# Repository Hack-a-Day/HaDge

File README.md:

# HaDge
=======
A wearable thing for Hackaday folks.

We're building a conference badge. No, we're not planning on organizing a Hackaday conference. It's for all the other conferences Hackaday goes to. If you have this badge, you're a member of an elite club, able to socialize in meatspace just as easily as you do on .io.

https://hackaday.io/project/3009-the-hackaday-badge

License
-------
[CERN Open Hardware Licence v1.2 ]

[CERN Open Hardware Licence v1.2 ]:http://www.ohwr.org/attachments/2388/cern_ohl_v_1_2.txt

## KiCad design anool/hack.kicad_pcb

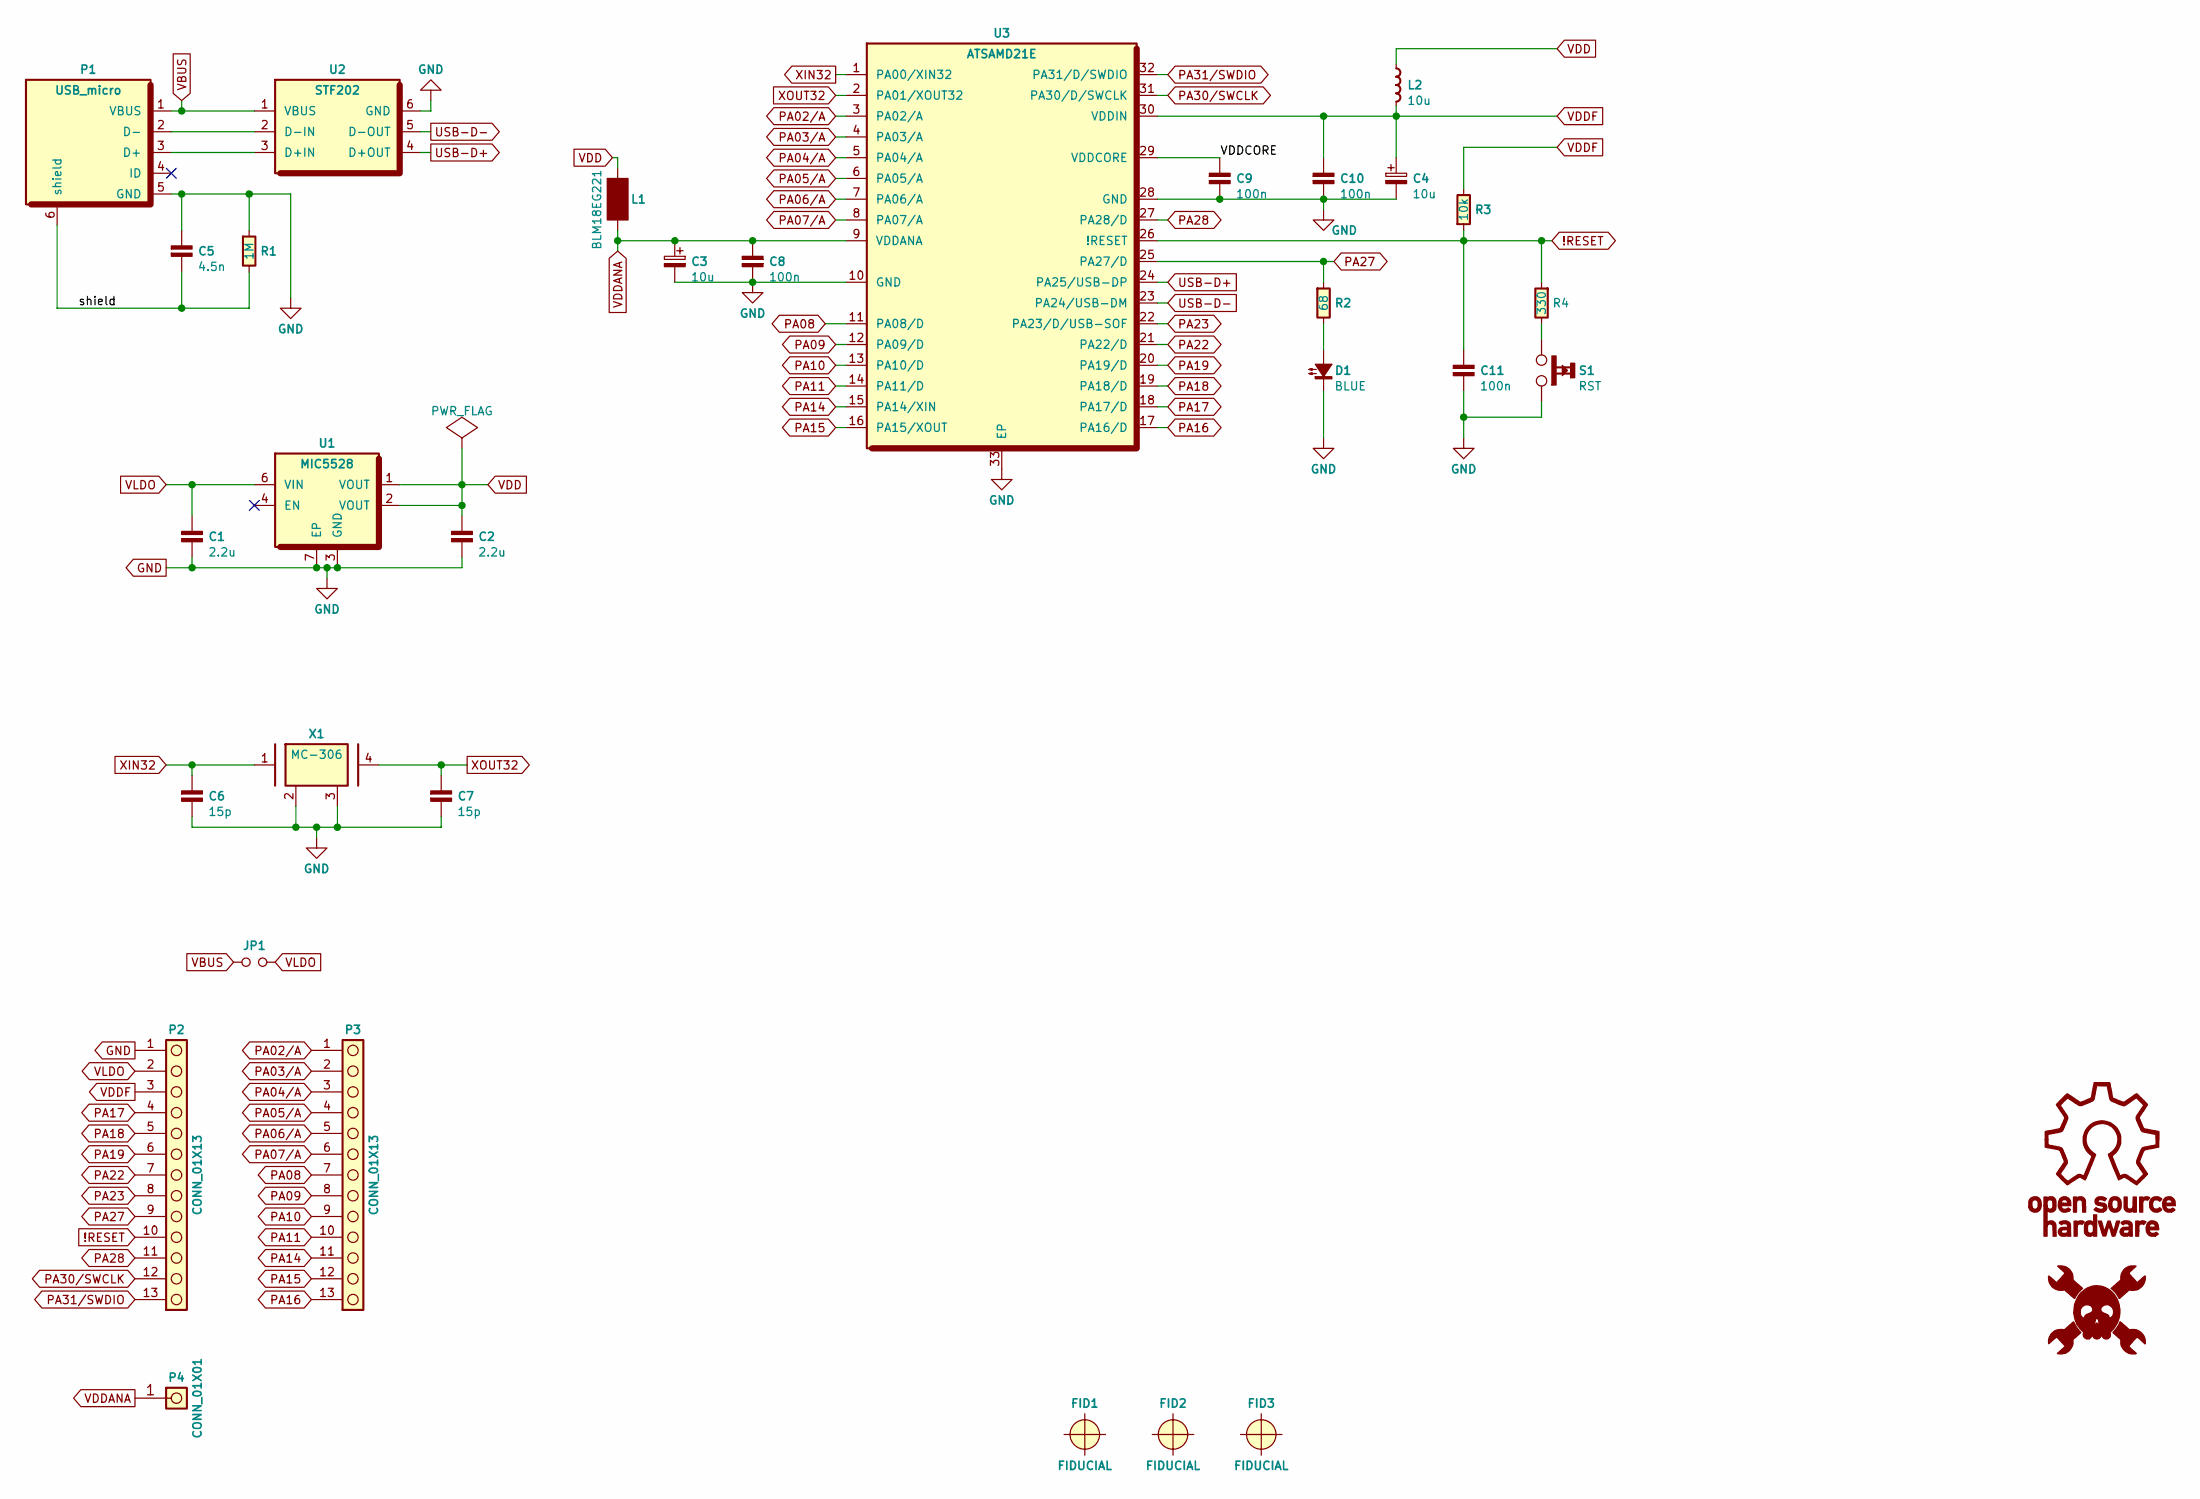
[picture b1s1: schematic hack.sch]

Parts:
C1, C2: 2.2u; C_0603_HandSoldering
C3, C4: 10u; c_elec_3x5.3
C5: 4.5n; C_0603_HandSoldering
C6, C7: 15p; C_0603_HandSoldering
C8, C9, C10, C11: 100n; C_0603_HandSoldering
D1: BLUE; LED_0603_HandSoldering
FID1, FID2, FID3: FIDUCIAL
G1: OSHW; OSHW-LOGO
G2: HACKADAY; HACKADAY-LOGO
JP1: Jumper_NO_Small; SMD_Jumper
L1: BLM18EG221; L_0603_HandSoldering
L2: 10u; ELLVFG
P1: USB_micro; 47346-0001
P2, P3: CONN_01X13; Pin_Header_Straight_1x13
P4: CONN_01X01; Pin_Header_Straight_1x01
R1: 1M; R_0603_HandSoldering
R2: 68; R_0603_HandSoldering
R3: 10k; R_0603_HandSoldering
R4: 330; R_0603_HandSoldering
S1: RST; SPST
U1: MIC5528; DFN-6-1EP_1.2x1.2mm_Pitch0.4mm
U2: STF202; TSOP-6
U3: ATSAMD21E; QFN-32-1EP_5x5mm_Pitch0.5mm
X1: MC-306

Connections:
!RESET: C11.1, P2.10, R3.1, R4.1, U3.26 (!RESET)
/VDDCORE: C9.1, U3.29 (VDDCORE)
/shield: C5.2, P1.6 (shield), R1.2
GND: C1.2, C2.2, C3.2, C4.2, C5.1, C6.2, C7.2, C8.2, C9.2, C10.2, C11.2, D1.1 (K), P1.5 (GND), P2.1, R1.1, S1.1, U1.3 (GND), U1.7 (EP), U2.6 (GND), U3.10 (GND), U3.28 (GND), U3.33 (EP), X1.2, X1.3
unnamed: D1.2 (A), R2.2
unnamed: P1.2 (D-), U2.2 (D-IN)
unnamed: P1.3 (D+), U2.3 (D+IN)
unnamed: R4.2, S1.2
PA02/A: P3.1, U3.3 (PA02/A)
PA03/A: P3.2, U3.4 (PA03/A)
PA04/A: P3.3, U3.5 (PA04/A)
PA05/A: P3.4, U3.6 (PA05/A)
PA06/A: P3.5, U3.7 (PA06/A)
PA07/A: P3.6, U3.8 (PA07/A)
PA08: P3.7, U3.11 (PA08/D)
PA09: P3.8, U3.12 (PA09/D)
PA10: P3.9, U3.13 (PA10/D)
PA11: P3.10, U3.14 (PA11/D)
PA14: P3.11, U3.15 (PA14/XIN)
PA15: P3.12, U3.16 (PA15/XOUT)
PA16: P3.13, U3.17 (PA16/D)
PA17: P2.4, U3.18 (PA17/D)
PA18: P2.5, U3.19 (PA18/D)
PA19: P2.6, U3.20 (PA19/D)
PA22: P2.7, U3.21 (PA22/D)
PA23: P2.8, U3.22 (PA23/D/USB-SOF)
PA27: P2.9, R2.1, U3.25 (PA27/D)
PA28: P2.11, U3.27 (PA28/D)
PA30/SWCLK: P2.12, U3.31 (PA30/D/SWCLK)
PA31/SWDIO: P2.13, U3.32 (PA31/D/SWDIO)
USB-D+: U2.4 (D+OUT), U3.24 (PA25/USB-DP)
USB-D-: U2.5 (D-OUT), U3.23 (PA24/USB-DM)
VBUS: JP1.1, P1.1 (VBUS), U2.1 (VBUS)
VDD: C2.1, L1.1, L2.1, U1.1 (VOUT), U1.2 (VOUT)
VDDANA: C3.1, C8.1, L1.2, P4.1, U3.9 (VDDANA)
VDDF: C4.1, C10.1, L2.2, P2.3, R3.2, U3.30 (VDDIN)
VLDO: C1.1, JP1.2, P2.2, U1.6 (VIN)
XIN32: C6.1, U3.1 (PA00/XIN32), X1.1
XOUT32: C7.1, U3.2 (PA01/XOUT32), X1.4

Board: 2 copper layers, 33 parts (6 on the bottom side), 39 nets, no tracks yet.

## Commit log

2015-08-23 first commit. Setup HW,SW,FW folders
2015-12-10 work in progress
2015-12-21 moved all of Anool's kicad HaDge files to 'anool' folder
2015-12-28 added HACK schematic layout
